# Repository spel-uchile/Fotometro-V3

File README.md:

# Sun Photometer V3
 This is the Low Cost Aotumatic LED-Based Sun Photometer (LoCo-ASP) Repository. There are the master files to manufacture the prototypes. Furhtermore, al the algorithms to calibrate the instruments are included.
 Everyone can use those documents, but there is not warranty.

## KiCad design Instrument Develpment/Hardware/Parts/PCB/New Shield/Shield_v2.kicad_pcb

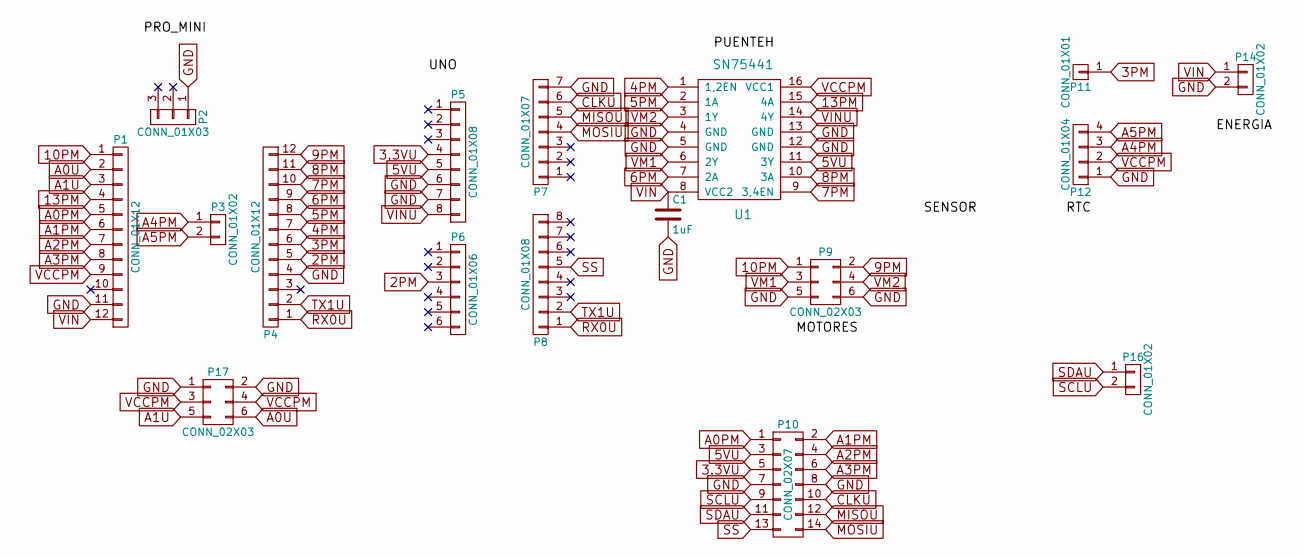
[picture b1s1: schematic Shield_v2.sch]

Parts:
C1: 1uF; C_Disc_D3_P2.5
P1, P4: CONN_01X12; Pin_Header_Straight_1x12
P2: CONN_01X03; Pin_Header_Straight_1x03
P3, P16: CONN_01X02; Pin_Header_Straight_1x02
P5, P8: CONN_01X08; Pin_Header_Straight_1x08
P6: CONN_01X06; Pin_Header_Straight_1x06
P7: CONN_01X07; Pin_Header_Straight_1x07
P9: CONN_02X03; Pin_Header_Angled_2x03
P10: CONN_02X07; Pin_Header_Angled_2x07
P11: CONN_01X01; Pin_Header_Straight_1x01
P12: CONN_01X04; Pin_Header_Straight_1x04
P14: CONN_01X02; Pin_Header_Angled_1x02
P17: CONN_02X03; Socket_Strip_Angled_2x03
U1: SN75441; DIP-16_W7.62mm_LongPads

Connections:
2PM: P4.5, P6.3
3.3VU: P5.4, P10.5
3PM: P4.6, P11.1
4PM: P4.7, U1.1 (1,2EN)
5PM: P4.8, U1.2 (1A)
5VU: P5.5, P10.3, U1.11 (3Y)
6PM: P4.9, U1.7 (2A)
7PM: P4.10, U1.9 (3,4EN)
8PM: P4.11, U1.10 (3A)
9PM: P4.12, P9.2
10PM: P1.1, P9.1
13PM: P1.4, U1.15 (4A)
A0PM: P1.5, P10.1
A0U: P1.2, P17.6
A1PM: P1.6, P10.2
A1U: P1.3, P17.5
A2PM: P1.7, P10.4
A3PM: P1.8, P10.6
A4PM: P3.1, P12.3
A5PM: P3.2, P12.4
CLKU: P7.6, P10.10
GND: C1.2, P1.11, P2.1, P4.4, P5.6, P5.7, P7.7, P9.5, P9.6, P10.7, P10.8, P12.1, P14.2, P17.1, P17.2, U1.4 (GND), U1.5 (GND), U1.12 (GND), U1.13 (GND)
MISOU: P7.5, P10.12
MOSIU: P7.4, P10.14
RX0U: P4.1, P8.1
SCLU: P10.9, P16.2
SDAU: P10.11, P16.1
SS: P8.5, P10.13
TX1U: P4.2, P8.2
VCCPM: P1.9, P12.2, P17.3, P17.4, U1.16 (VCC1)
VIN: C1.1, P1.12, P14.1, U1.8 (VCC2)
VINU: P5.8, U1.14 (4Y)
VM1: P9.3, U1.6 (2Y)
VM2: P9.4, U1.3 (1Y)

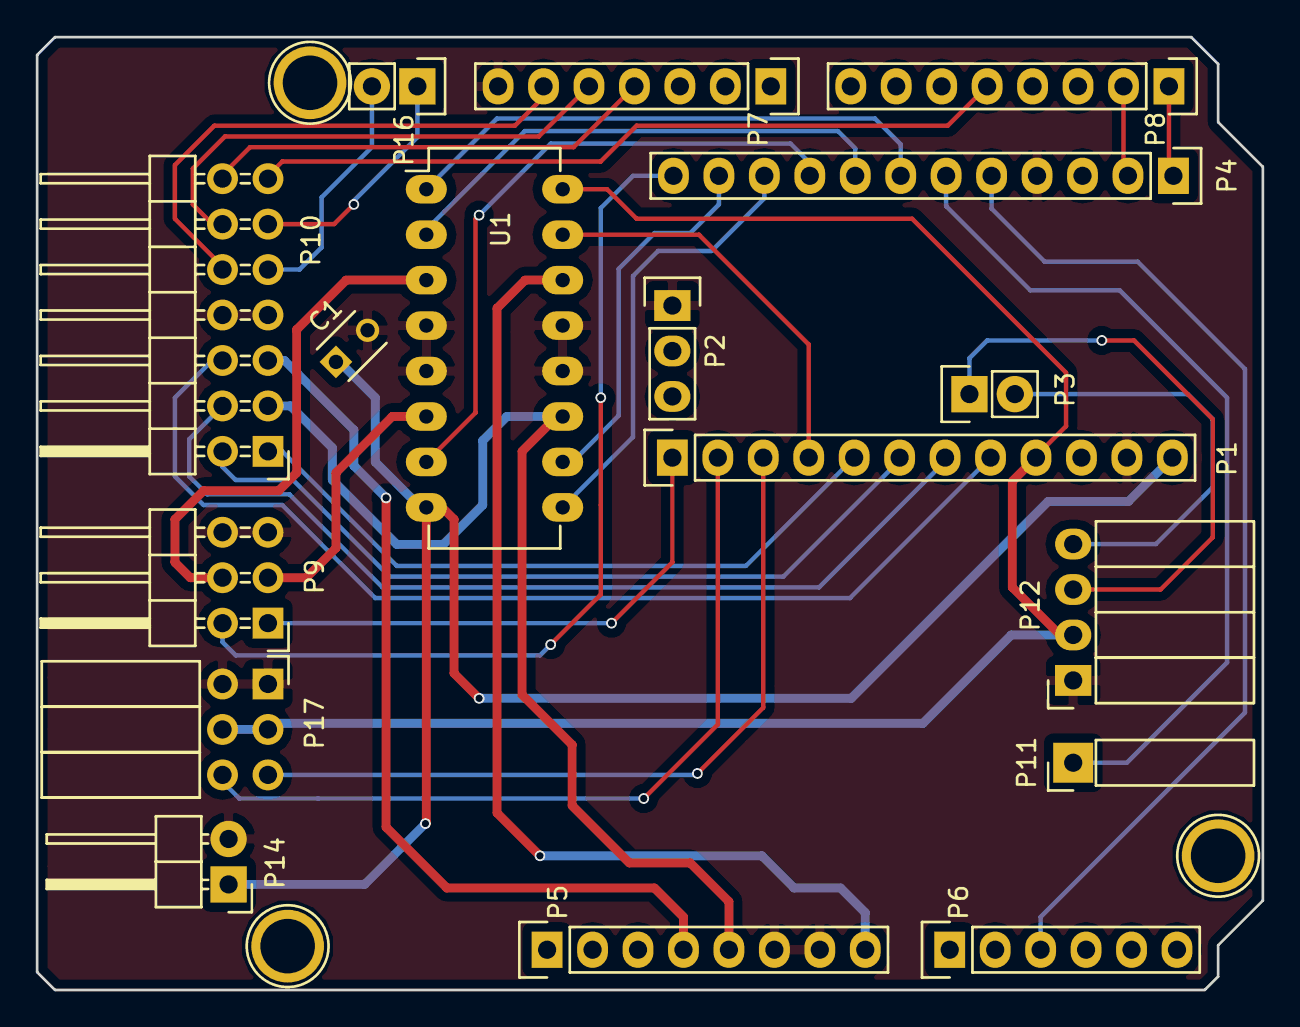
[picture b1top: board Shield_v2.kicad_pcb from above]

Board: 2 copper layers, 68.5 x 53.2 mm, 17 parts (0 on the bottom side), 34 nets.

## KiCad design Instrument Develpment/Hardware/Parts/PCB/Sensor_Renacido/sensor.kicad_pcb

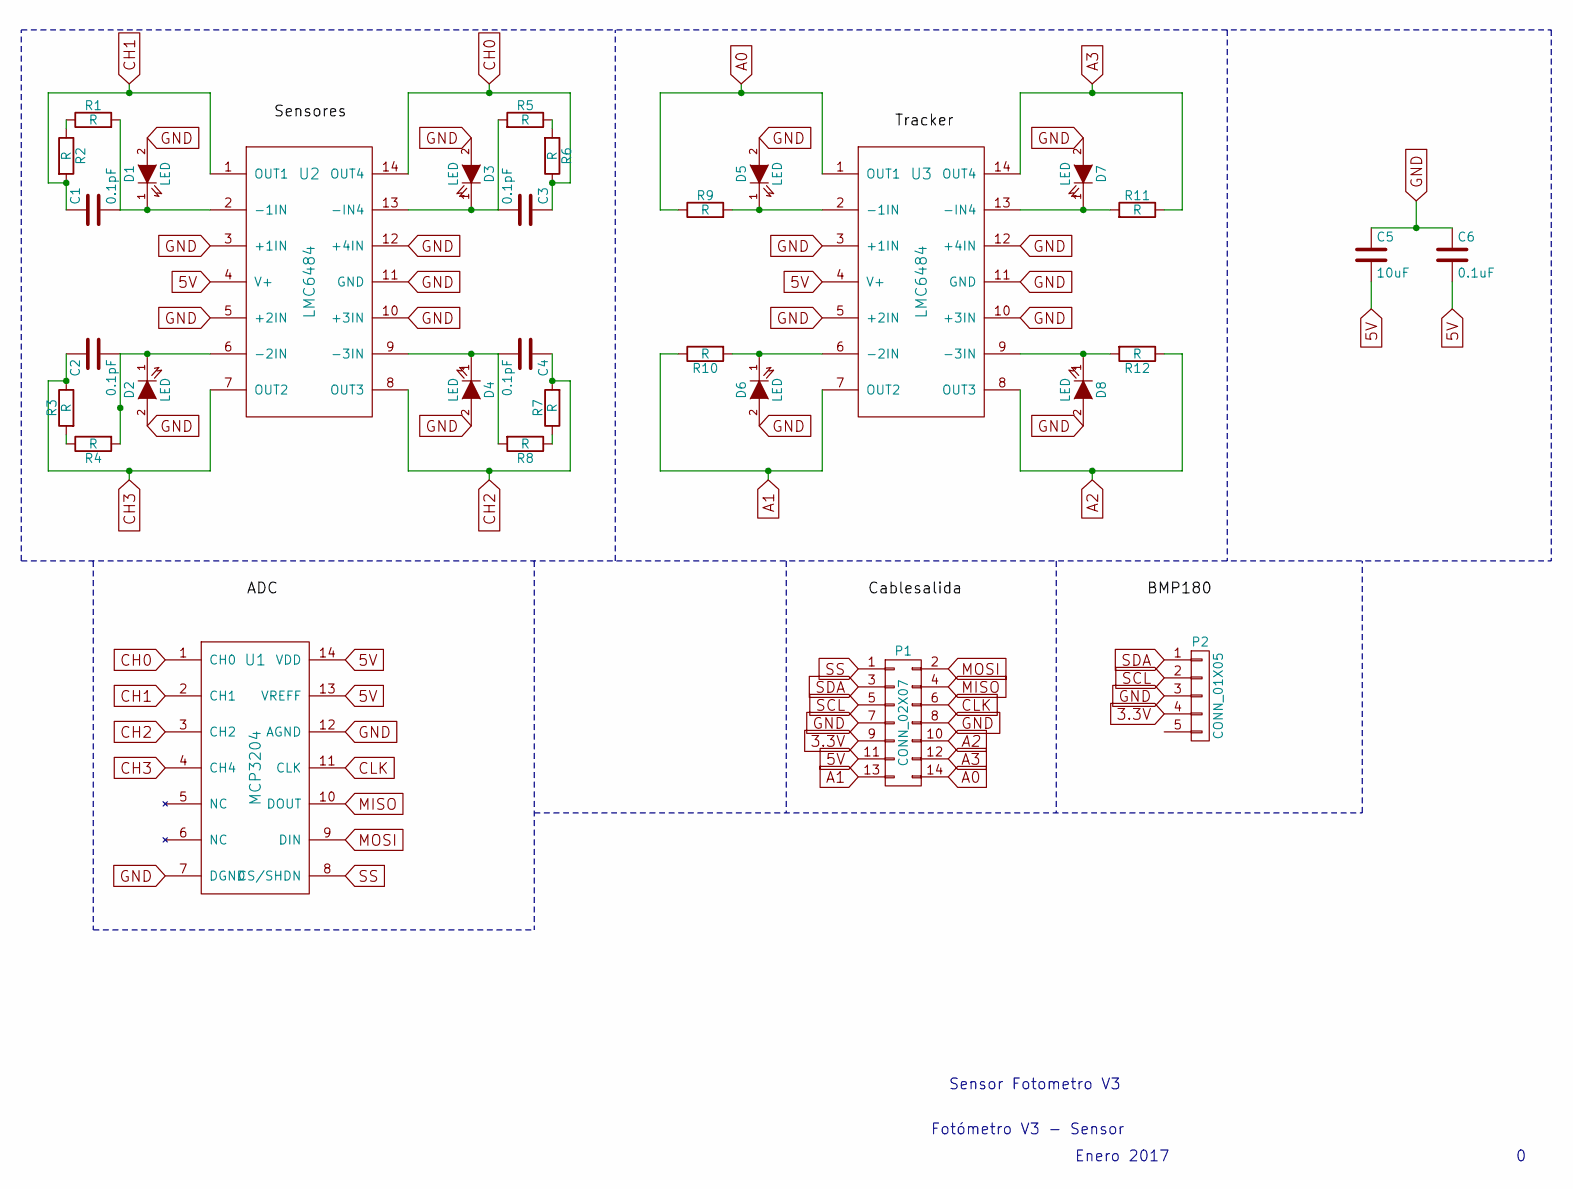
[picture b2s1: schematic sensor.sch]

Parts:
C1, C2, C3, C4: 0.1pF; C_0603_HandSoldering
C5: 10uF; C_1206_HandSoldering
C6: 0.1uF; C_1206_HandSoldering
D1, D2, D3, D4, D5, D6, D7, D8: LED; LED-5MM
P1: CONN_02X07; Pin_Header_Straight_2x07
P2: CONN_01X05; Pin_Header_Straight_1x05
R1, R2, R3, R4, R5, R6, R7, R8, R9, R10, R11, R12: R; Resistor_Horizontal_RM7mm
U1: MCP3204; SOIC-14_3.9x8.7mm_Pitch1.27mm
U2, U3: LMC6484; SOIC-14_3.9x8.7mm_Pitch1.27mm

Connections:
3.3V: P1.9, P2.4
5V: C5.2, C6.2, P1.11, U1.13 (VREFF), U1.14 (VDD), U2.4 (V+), U3.4 (V+)
A0: P1.14, R9.1, U3.1 (OUT1)
A1: P1.13, R10.1, U3.7 (OUT2)
A2: P1.10, R12.1, U3.8 (OUT3)
A3: P1.12, R11.1, U3.14 (OUT4)
CH0: C3.1, R6.1, U1.1 (CH0), U2.14 (OUT4)
CH1: C1.1, R2.2, U1.2 (CH1), U2.1 (OUT1)
CH2: C4.1, R7.2, U1.3 (CH2), U2.8 (OUT3)
CH3: C2.1, R3.1, U1.4 (CH4), U2.7 (OUT2)
CLK: P1.6, U1.11 (CLK)
GND: C5.1, C6.1, D1.2 (A), D2.2 (A), D3.2 (A), D4.2 (A), D5.2 (A), D6.2 (A), D7.2 (A), D8.2 (A), P1.7, P1.8, P2.3, U1.7 (DGND), U1.12 (AGND), U2.3 (+1IN), U2.5 (+2IN), U2.10 (+3IN), U2.11 (GND), U2.12 (+4IN), U3.3 (+1IN), U3.5 (+2IN), U3.10 (+3IN), U3.11 (GND), U3.12 (+4IN)
MISO: P1.4, U1.10 (DOUT)
MOSI: P1.2, U1.9 (DIN)
unnamed: C1.2, D1.1 (K), R1.2, U2.2 (-1IN)
unnamed: C2.2, D2.1 (K), R4.2, U2.6 (-2IN)
unnamed: C3.2, D3.1 (K), R5.2, U2.13 (-IN4)
unnamed: C4.2, D4.1 (K), R8.2, U2.9 (-3IN)
unnamed: D5.1 (K), R9.2, U3.2 (-1IN)
unnamed: D6.1 (K), R10.2, U3.6 (-2IN)
unnamed: D7.1 (K), R11.2, U3.13 (-IN4)
unnamed: D8.1 (K), R12.2, U3.9 (-3IN)
unnamed: R1.1, R2.1
unnamed: R3.2, R4.1
unnamed: R5.1, R6.2
unnamed: R7.1, R8.1
SCL: P1.5, P2.2
SDA: P1.3, P2.1
SS: P1.1, U1.8 (CS/SHDN)

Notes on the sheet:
Sensor Fotometro V3
Fotómetro V3 - Sensor
Enero 2017

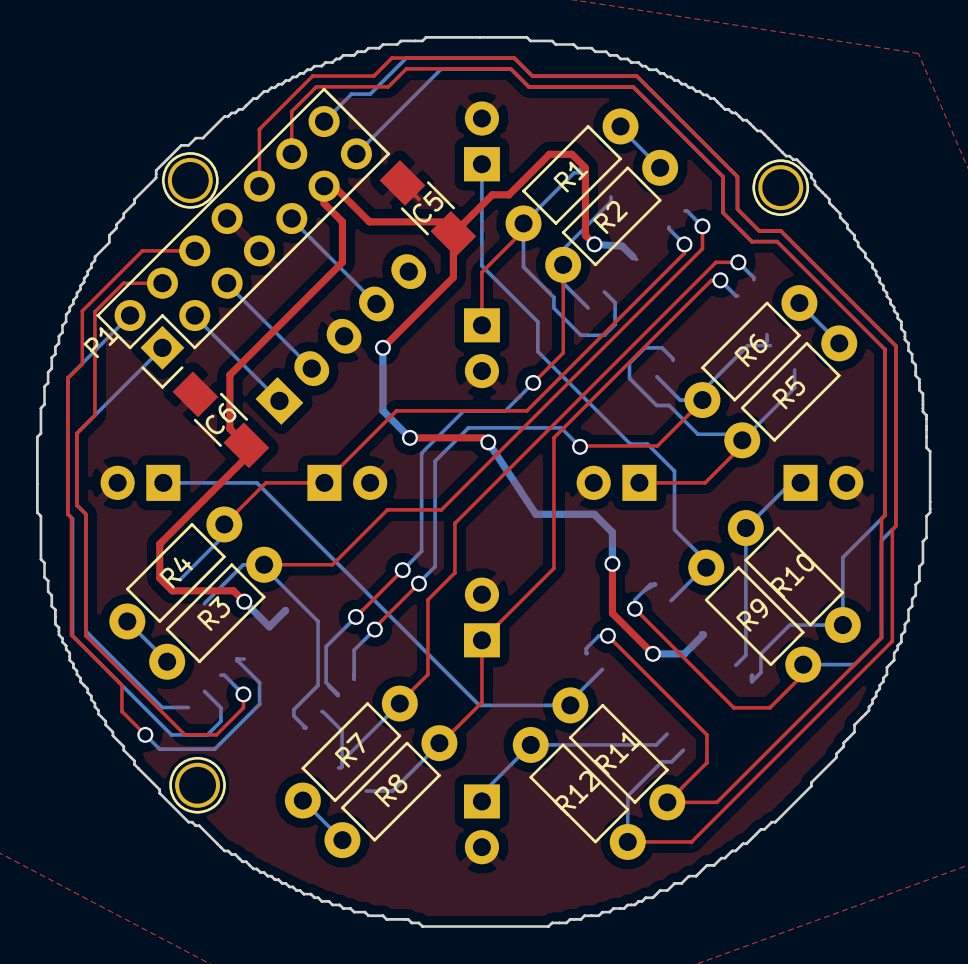
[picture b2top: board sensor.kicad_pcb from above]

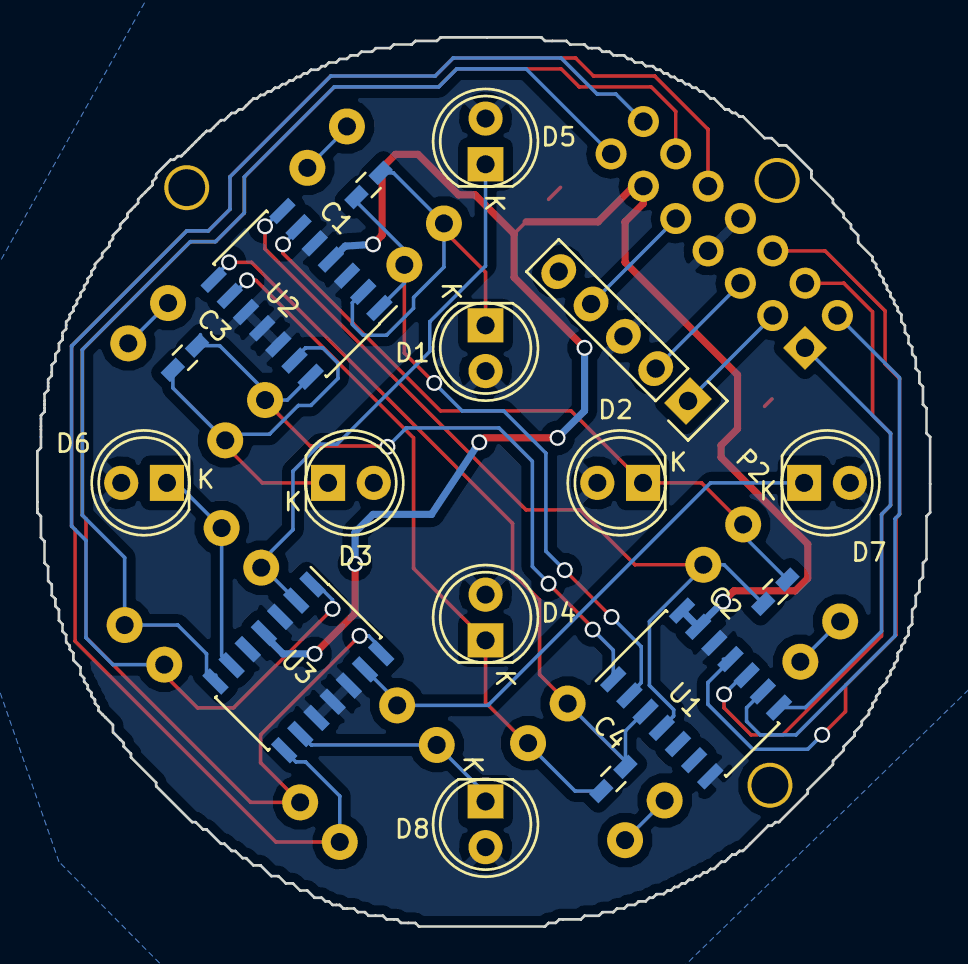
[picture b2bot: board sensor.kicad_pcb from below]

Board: 2 copper layers, 49.6 x 49.4 mm, 31 parts (16 on the bottom side), 29 nets.

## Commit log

2020-06-02 First Commit
    Software elements
2020-06-02 Hardware Commit
    All pieces to be printed
2020-06-02 third commit
    data analyzis
2020-06-07 Tracker V3
    Included Uploadble version of the Sun Tracker
2021-09-30 Update README.md
    Name update
2021-10-20 Update README.md
    mere information
2021-11-05 New figures and programs
    According to revisions of the article, qe updated some code to meke easier to understand the concept
